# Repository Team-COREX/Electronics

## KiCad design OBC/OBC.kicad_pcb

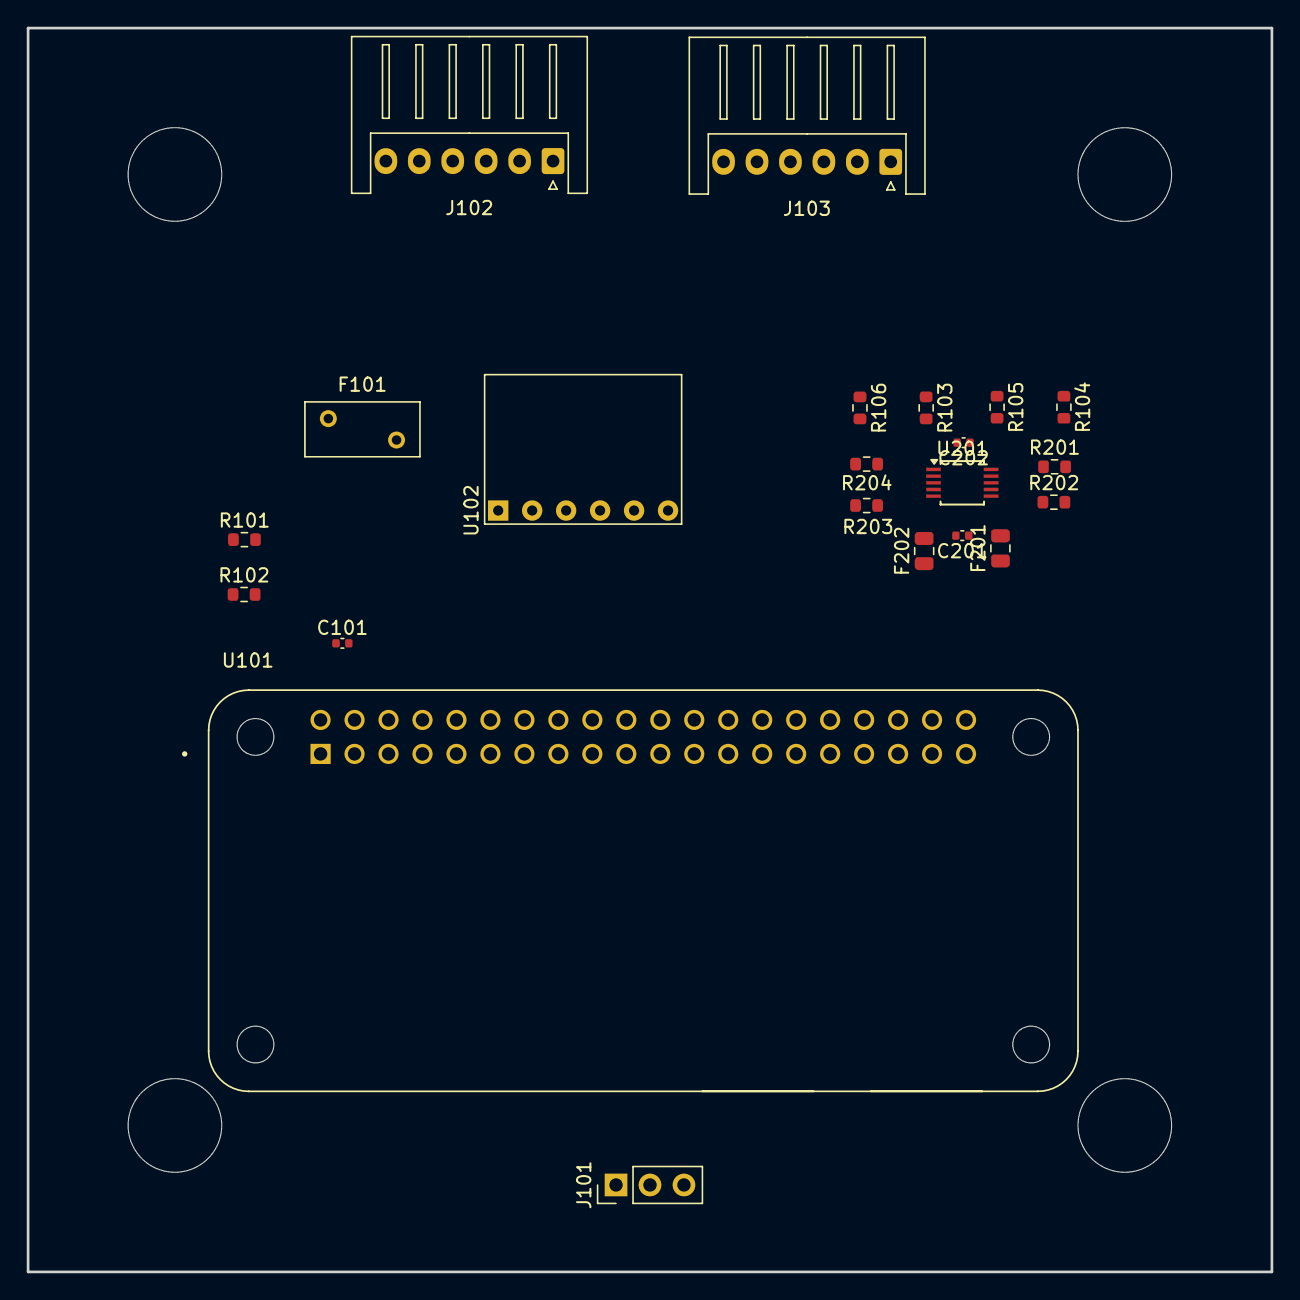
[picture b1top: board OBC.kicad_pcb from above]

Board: 2 copper layers, 93.0 x 93.0 mm, 22 parts (0 on the bottom side), 15 nets, no tracks yet.

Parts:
C101: C_Small; C_0402_1005Metric
C201, C202: 100nF; C_0402_1005Metric
F101: Fuse; Fuse_BelFuse_0ZRE0005FF_L8.3mm_W3.8mm
F201, F202: Fuse; Fuse_0805_2012Metric
J101: Conector UART; PinHeader_1x03_P2.54mm_Vertical
J102: PMS-Raspi; JST_XH_S6B-XH-A_1x06_P2.50mm_Horizontal
J103: Raspi-TRU; JST_XH_S6B-XH-A_1x06_P2.50mm_Horizontal
R101, R102, R103, R104, R105: R; R_0603_1608Metric
R106, R201, R202, R203, R204: 10k; R_0603_1608Metric
U101: RASPBERRY_PI_ZERO_2_W; MODULE_RASPBERRY_PI_ZERO_2_W
U102: BMP280; BMP280_Module
U201: ADS1115IDGS; TSSOP-10_3x3mm_P0.5mm

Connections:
+3.3V PMS: C201.1, F201.1, J102.4, R101.1, R102.1, U102.1 (VCC)
+5V PMS: F101.2, J102.5, J103.6
/ADS1115_ADC/ADDR: R204.2, U201.1 (ADDR)
/AIN0: J103.1, R103.1, U201.4 (AIN0)
/AIN1: J103.2, R104.1, U201.5 (AIN1)
/AIN2: J103.3, R105.1, U201.6 (AIN2)
/I2C_SCL: J102.2, R102.2, R201.1, U101.5 (GPIO3/SCL), U102.3 (SCL), U201.10 (SCL)
/I2C_SDA: J102.1, R101.2, R202.1, U101.3 (GPIO2/SDA1), U102.4 (SDA), U201.9 (SDA)
/INT_ADC: R203.1, U101.31 (GPIO6), U201.2 (ALERT/RDY)
/RXD: J101.1, U101.10 (GPIO15/RXD0)
/TXD: J101.3, U101.8 (GPIO14/TXD0)
GND: C101.2, C201.2, F202.1, J101.2, J102.3, J102.6, R103.2, R104.2, R105.2, R106.2, U101.6 (GND_6), U101.9 (GND_9), U101.14 (GND_14), U101.20 (GND_20), U101.25 (GND_25), U101.30 (GND_30), U101.34 (GND_34), U101.39 (GND_39), U102.2 (GND)
unnamed: C101.1, F101.1, U101.2 (5V_2), U101.4 (5V_4)
unnamed: C202.2, F202.2, R204.1, U201.3 (GND)
unnamed: C202.1, F201.2, R201.2, R202.2, R203.2, U201.8 (VDD)

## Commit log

2025-07-17 Crea archivo kicad para OBC
2025-07-17 Agrega simbolo MPU9250
2025-07-27 Agrega símbolo de rpi pi zero 2w
2025-07-27 Agrega footprint de BMP280
2025-07-27 Agrega módulo ADC
2025-07-27 Cambia global labels por hier labels ADC
2025-07-28 Agrega resistencias pull-up para I2C
2025-07-29 Agrega conector para UART
2025-07-29 Agrega sch de ADS1115
2025-07-29 Organiza sch general
2025-07-29 Coloca pinout para UART
2025-08-02 Conecta pines int a gpio
2025-08-02 Agrega no connect flags
2025-08-02 Actualiza numeración de componentes
2025-08-02 Agrega pwr flags
2025-08-02 Agrega footprint rpi
2025-08-04 Cambia conectores IDC por JST
2025-08-04 Agrega resistencias en serie con NTC
2025-08-05 Crea proyecto del PMS en kicad
2025-08-05 Quita conector del sch del ADC
2025-08-05 Empieza con pcb
2025-08-05 Propone disposicion pcb
2025-08-06 Cambia disposición del selector de modos
2025-08-06 Revisión v1.0
2025-08-08 Crea simulacion de seleccion de fuentes
2025-08-08 Diseña seleccion de entrada y regulacion
2025-08-08 Define ciertos pines y diseña mediciones
2025-08-08 Continua Desarrollo
2025-08-09 Diseña sensor de corriente y puentes H
2025-08-09 Cambia sensor de corriente
2025-08-09 Correcciones menores
2025-08-09 Correcciones menores
    mentirillas
2025-08-15 Remueve hmi fisico del obs y renombra componentes
2025-08-15 Agrega HMI y expansor I2C
